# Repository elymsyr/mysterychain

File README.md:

# MysteryChain

A small hobby project: a virtual pet that lives on a keychain. A round 1.28" screen, a vibration motor and a tiny battery in a 3D-printed case about 4 cm across, paired with an Android app over Bluetooth.

- A pixel pet on the screen: a cat, or one of a few other characters picked in the app. It gets hungry, sleepy and happy through the day.
- Shake it and the pet plays; tap the case twice to pet it. It counts your steps too.
- Messages from your phone pop up in a speech bubble, along with the time, the weather and the song that's playing.
- One button: tap for the clock, hold to turn it on or off.

**Status:** works on the breadboard. The case is test-printed; nothing is assembled in it yet.

## Building one

Parts, wiring, flashing the firmware, the app and the case are in the [developer introduction](docs/developers.md).

## License

[GPL-3.0](LICENSE)

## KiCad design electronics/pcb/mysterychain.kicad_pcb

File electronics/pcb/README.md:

# MysteryChain PCB rev A

KiCad 9 project for the custom board that replaces the XIAO nRF52840 Sense build.
Design: [2026-10-20-pcb-design.md](../../docs/superpowers/specs/2026-10-20-pcb-design.md).

## Case v8 inputs

Case coordinates: origin = display centre, +X right, +Y toward the lug, looking at the display.
Front = display side, back = midframe side. The board is 1.0 mm thick.

| Item | Value |
| --- | --- |
| Outline | `gen_pcb.outline()`: circle r 18.0, cut at Y +7.0, J1 tongue X ±5.6 down to Y −18.2, Ø3.0 notches at r 17.6 / 205° and 335° |
| J1 (USB-C, back) | face on Y −18.2, X 0, opening −Y; GCT USB4105, 3.31 mm above the back face |
| H1, H2 | NPTH Ø2.0 at (−6.2, −14.8) and (6.2, −14.8): case v8 locating pins take the USB plug force |
| SW1 (button, back) | C&K KMS221GP side-actuated, body centre (−16.22, 0), plunger tip at X −18.37, axis Y 0, about 0.7 mm above the back face (half the 1.42 mm body) |
| SW2 (battery switch, back) | EG1390 body centre (−10.55, −7.0), slide along Y; v7 had (−11.25, −7.0): its pads would cut the 205° notch, so the slot moves 0.7 mm +X |
| SW3 (reset, back) | C&K PTS810 centre (8.6, −11.7), 2.5 mm tall; the midframe reset hole moves here (no room left of J1) |
| E73 (back) | body X −3.9…14.1, Y −8.2…4.8, 3.0 mm tall, antenna end at +X |
| J3 battery / J4 motor pads | back, top edge: J3 at (−13.5, 5.5) B+ / B−, J4 at (−9.5, 5.5) M+ / M− |
| J2 display pads | front, top edge, X −15.6…−3.6 at Y 5.5, pad 1 (VCC) at X −3.6 |
| U2 (IMU, front) | LSM6DS3TR-C at (−11.0, −1.4), rotation 0, on the front: its Z axis points at the display, opposite the XIAO's |

## ERC warnings kept

`check.py sch` fails on any ERC error and on any warning type not listed here.

| Warning | Where | Why it stays |
| --- | --- | --- |
| `pin_to_pin` | U1 pad 33 (P0.13, bidirectional) + PWR_FLAG on IMU_PWR | The IMU is powered from a GPIO (spec: 0 µA when off). The flag tells ERC the rail has a source. |
| `pin_to_pin` | U2 pins 1/2 (SA0, SDx, bidirectional) + PWR_FLAG on GND | SA0 and SDx are tied to GND on purpose (address 0x6A, aux bus unused). |

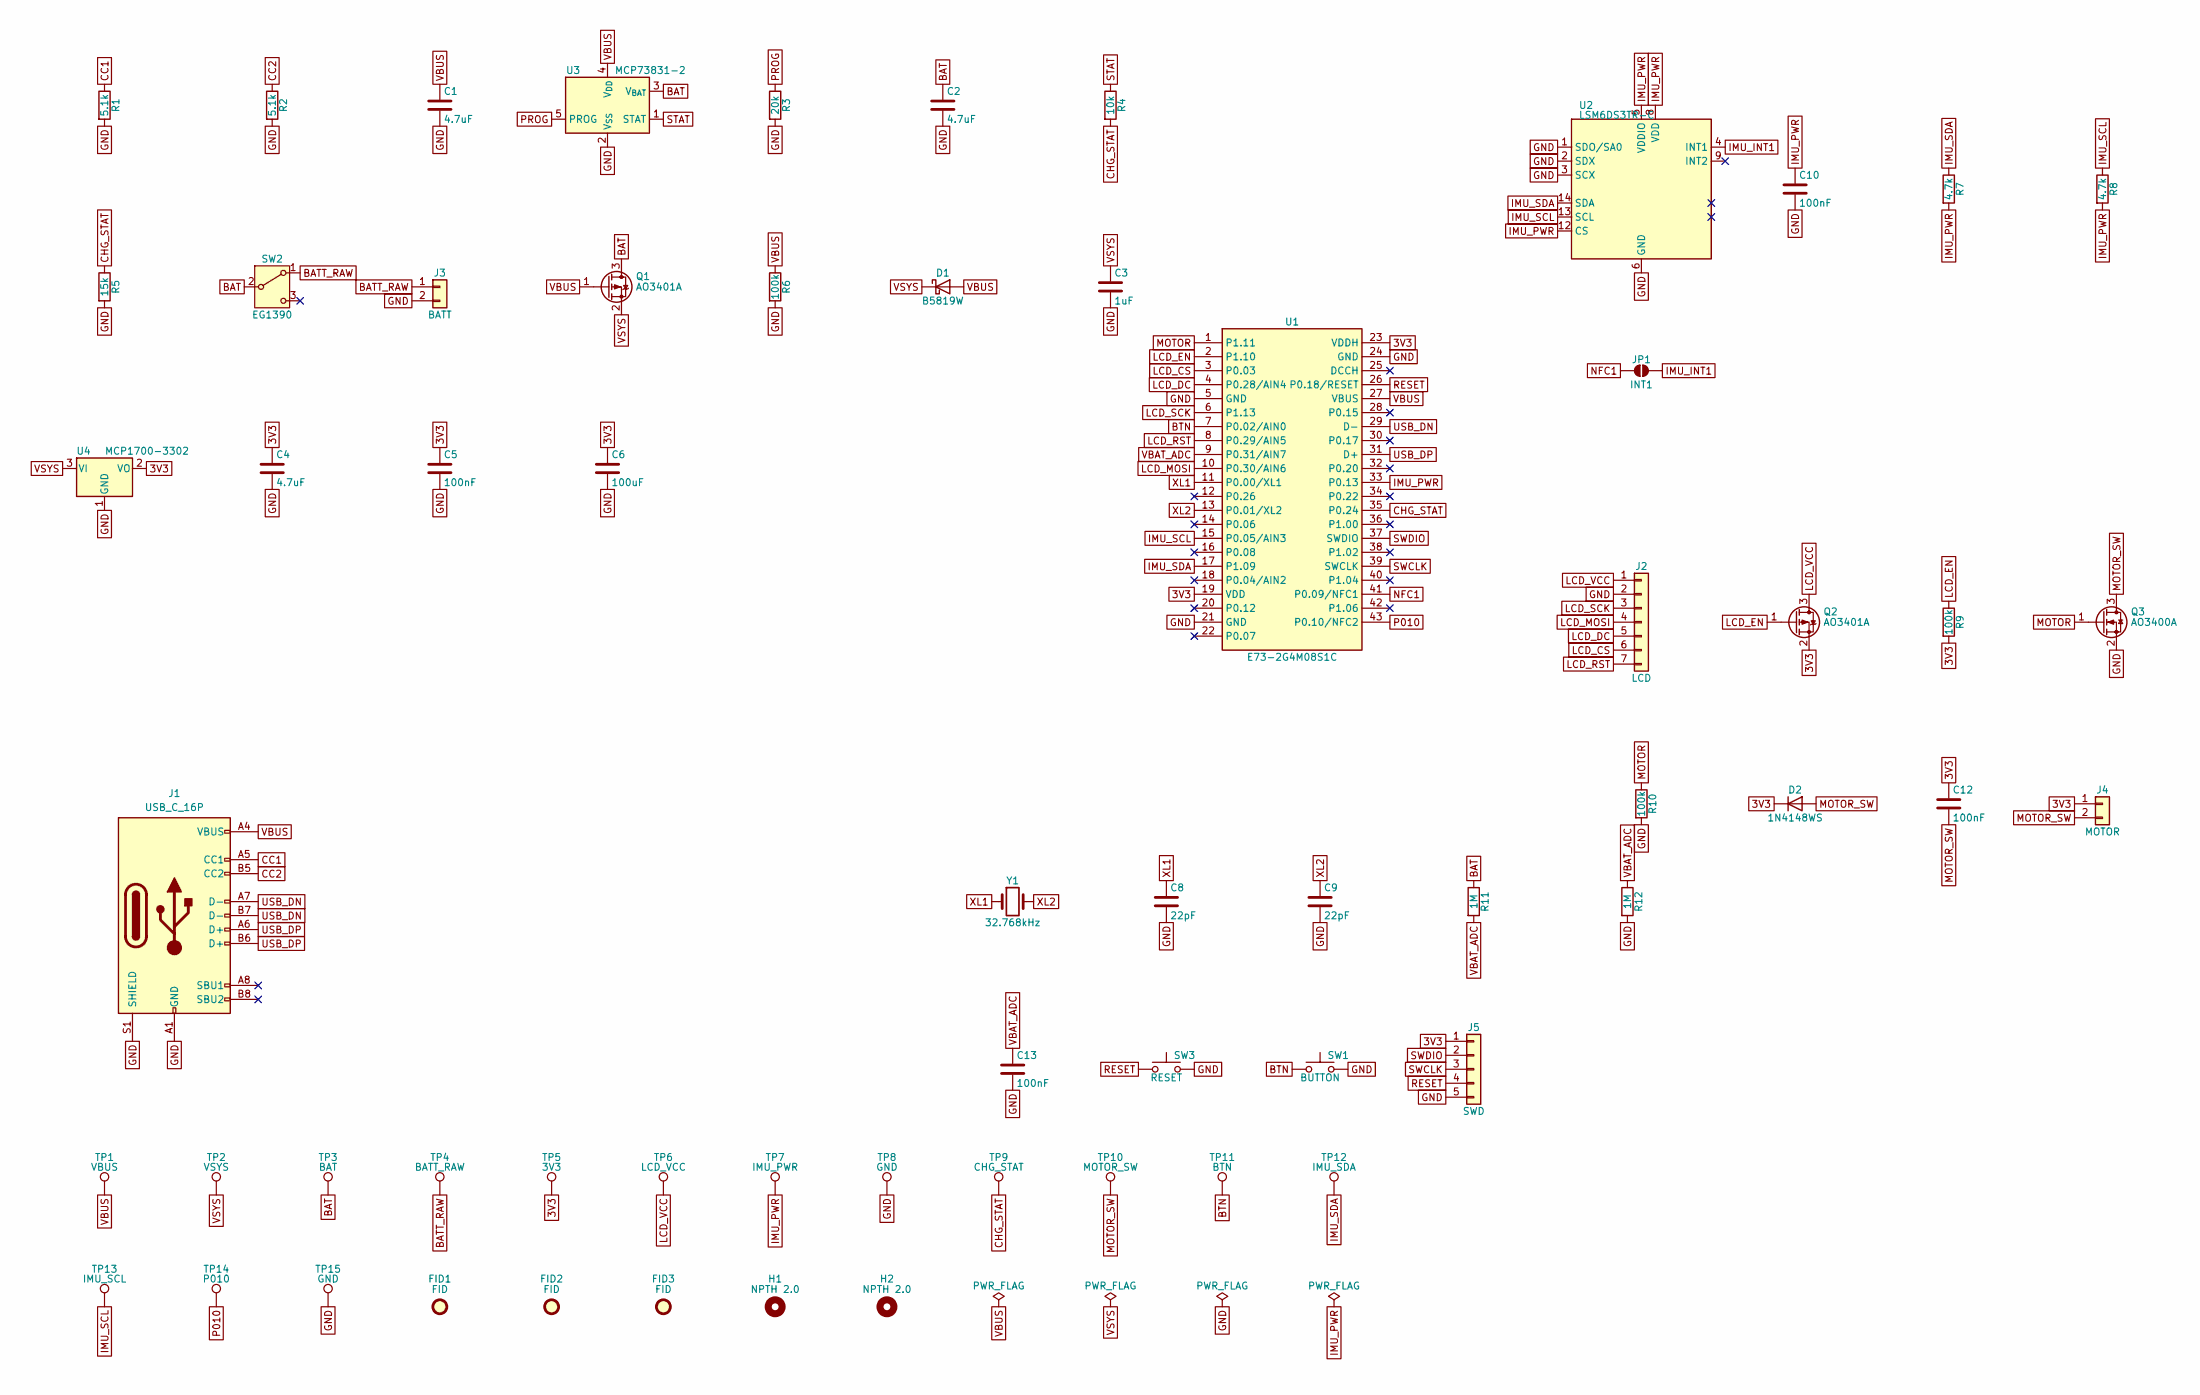
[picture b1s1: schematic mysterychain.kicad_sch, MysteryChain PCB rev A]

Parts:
C1, C2, C4: 4.7uF; C_0603_1608Metric; MPN 0603 X5R/X7R 10 V, 4.7uF
C3: 1uF; C_0603_1608Metric; MPN 0603 X5R/X7R 10 V, 1uF
C5, C10, C12, C13: 100nF; C_0603_1608Metric; MPN 0603 X5R/X7R 10 V, 100nF
C6: 100uF; C_1206_3216Metric; MPN Murata GRM31CR60J107KEA8L (1206 X5R 6.3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
C8, C9: 22pF; C_0603_1608Metric; MPN 0603 C0G 50 V, 22pF
D1: B5819W; D_SOD-123; MPN B5819W
D2: 1N4148WS; D_SOD-323; MPN 1N4148WS
FID1, FID2: FID; Fiducial_1mm_Mask2mm
FID3: FID; Fiducial_0.75mm_Mask1.5mm
H1, H2: NPTH 2.0; NPTH_D2.0mm
J1: USB_C_16P; USB_C_Receptacle_GCT_USB4105-xx-A_16P_TopMnt_Horizontal; MPN GCT USB4105-GF-A
J2: LCD; PadRow_1x07_P2.00mm; MPN wire pads: VCC GND SCL SDA DC CS RST (G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
J3: BATT; PadRow_1x02_P2.00mm; MPN wire pads (LiPo 402030 leads)
J4: MOTOR; PadRow_1x02_P2.00mm; MPN wire pads (vibration motor)
J5: SWD; PadRow_1x05_P2.54mm; MPN SWD pads 2.54 mm (pogo clip / held head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
JP1: INT1; SolderJumper-2_P1.3mm_Open_Pad1.0x1.5mm; MPN solder jumper, open
Q1, Q2: AO3401A; SOT-23; MPN AO3401A
Q3: AO3400A; SOT-23; MPN AO3400A
R1, R2: 5.1k; R_0603_1608Metric; MPN 0603 1% thick film, 5.1k (Yageo RC0603F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
R3: 20k; R_0603_1608Metric; MPN 0603 1% thick film, 20k (Yageo RC0603FR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
R4: 10k; R_0603_1608Metric; MPN 0603 1% thick film, 10k (Yageo RC0603FR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
R5: 15k; R_0603_1608Metric; MPN 0603 1% thick film, 15k (Yageo RC0603FR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
R6, R9, R10: 100k; R_0603_1608Metric; MPN 0603 1% thick film, 100k (Yageo RC0603F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
R7, R8: 4.7k; R_0603_1608Metric; MPN 0603 1% thick film, 4.7k (Yageo RC0603F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
R11, R12: 1M; R_0603_1608Metric; MPN 0603 1% thick film, 1M (Yageo RC0603FR-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
SW1: BUTTON; SW_SPST_CK_KMS2xxGP; MPN C&K KMS221GP LFS (side actuated)
SW2: EG1390; MPN E-Switch EG1390
SW3: RESET; SW_SPST_PTS810; MPN C&K PTS810SJK250SMTRLFS
TP1: VBUS; TestPad_D1.0mm; MPN bare pad
TP2: VSYS; TestPad_D1.0mm; MPN bare pad
TP3: BAT; TestPad_D1.0mm; MPN bare pad
TP4: BATT_RAW; TestPad_D1.0mm; MPN bare pad
TP5: 3V3; TestPad_D1.0mm; MPN bare pad
TP6: LCD_VCC; TestPad_D1.0mm; MPN bare pad
TP7: IMU_PWR; TestPad_D1.0mm; MPN bare pad
TP8, TP15: GND; TestPad_D1.0mm; MPN bare pad
TP9: CHG_STAT; TestPad_D1.0mm; MPN bare pad
TP10: MOTOR_SW; TestPad_D1.0mm; MPN bare pad
TP11: BTN; TestPad_D1.0mm; MPN bare pad
TP12: IMU_SDA; TestPad_D1.0mm; MPN bare pad
TP13: IMU_SCL; TestPad_D1.0mm; MPN bare pad
TP14: P010; TestPad_D1.0mm; MPN bare pad
U1: E73-2G4M08S1C; MPN Ebyte E73-2G4M08S1C
U2: LSM6DS3TR-C; LGA-14_3x2.5mm_P0.5mm_HandSolder; MPN ST LSM6DS3TR-C
U3: MCP73831-2; SOT-23-5; MPN MCP73831T-2ACI/OT
U4: MCP1700-3302; SOT-23; MPN MCP1700T-3302E/TT
Y1: 32.768kHz; Crystal_SMD_3215-2Pin_3.2x1.5mm; MPN RT3215-32.768-12.5-TR (CL 12.5 pF, 20 p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

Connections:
3V3: C4.1, C5.1, C6.1, C12.1, D2.1 (K), J4.1, J5.1, Q2.2 (S), R9.2, TP5.1, U1.19 (VDD), U1.23 (VDDH), U4.2 (VO)
BAT: C2.1, Q1.3 (D), R11.1, SW2.2 (B), TP3.1, U3.3 (V_{BAT})
BATT_RAW: J3.1, SW2.1 (A), TP4.1
BTN: SW1.1, TP11.1, U1.7 (P0.02/AIN0)
CC1: J1.A5 (CC1), R1.1
CC2: J1.B5 (CC2), R2.1
CHG_STAT: R4.2, R5.1, TP9.1, U1.35 (P0.24)
GND: C1.2, C2.2, C3.2, C4.2, C5.2, C6.2, C8.2, C9.2, C10.2, C13.2, J1.A1 (GND), J1.A12 (GND), J1.B1 (GND), J1.B12 (GND), J1.S1 (SHIELD), J2.2, J3.2, J5.5, Q3.2 (S), R1.2, R2.2, R3.2, R5.2, R6.2, R10.2, R12.2, SW1.2, SW3.2, TP8.1, TP15.1, U1.5 (GND), U1.21 (GND), U1.24 (GND), U2.1 (SDO/SA0), U2.2 (SDX), U2.3 (SCX), U2.6 (GND), U2.7 (GND), U3.2 (V_{SS}), U4.1 (GND)
IMU_INT1: JP1.2 (B), U2.4 (INT1)
IMU_PWR: C10.1, R7.2, R8.2, TP7.1, U1.33 (P0.13), U2.5 (VDDIO), U2.8 (VDD), U2.12 (CS)
IMU_SCL: R8.1, TP13.1, U1.15 (P0.05/AIN3), U2.13 (SCL)
IMU_SDA: R7.1, TP12.1, U1.17 (P1.09), U2.14 (SDA)
LCD_CS: J2.6, U1.3 (P0.03)
LCD_DC: J2.5, U1.4 (P0.28/AIN4)
LCD_EN: Q2.1 (G), R9.1, U1.2 (P1.10)
LCD_MOSI: J2.4, U1.10 (P0.30/AIN6)
LCD_RST: J2.7, U1.8 (P0.29/AIN5)
LCD_SCK: J2.3, U1.6 (P1.13)
LCD_VCC: J2.1, Q2.3 (D), TP6.1
MOTOR: Q3.1 (G), R10.1, U1.1 (P1.11)
MOTOR_SW: C12.2, D2.2 (A), J4.2, Q3.3 (D), TP10.1
NFC1: JP1.1 (A), U1.41 (P0.09/NFC1)
P010: TP14.1, U1.43 (P0.10/NFC2)
PROG: R3.1, U3.5 (PROG)
RESET: J5.4, SW3.1, U1.26 (P0.18/RESET)
STAT: R4.1, U3.1 (STAT)
SWCLK: J5.3, U1.39 (SWCLK)
SWDIO: J5.2, U1.37 (SWDIO)
USB_DN: J1.A7 (D-), J1.B7 (D-), U1.29 (D-)
USB_DP: J1.A6 (D+), J1.B6 (D+), U1.31 (D+)
VBAT_ADC: C13.1, R11.2, R12.1, U1.9 (P0.31/AIN7)
VBUS: C1.1, D1.2 (A), J1.A4 (VBUS), J1.A9 (VBUS), J1.B4 (VBUS), J1.B9 (VBUS), Q1.1 (G), R6.1, TP1.1, U1.27 (VBUS), U3.4 (V_{DD})
VSYS: C3.1, D1.1 (K), Q1.2 (S), TP2.1, U4.3 (VI)
XL1: C8.1, U1.11 (P0.00/XL1), Y1.1
XL2: C9.1, U1.13 (P0.01/XL2), Y1.2

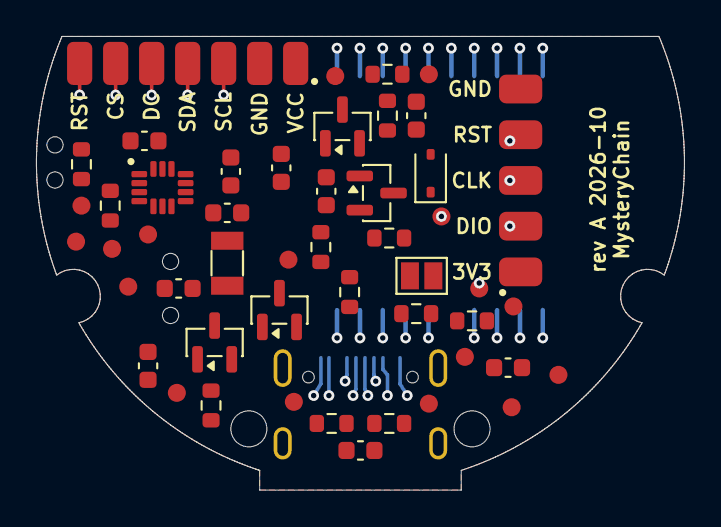
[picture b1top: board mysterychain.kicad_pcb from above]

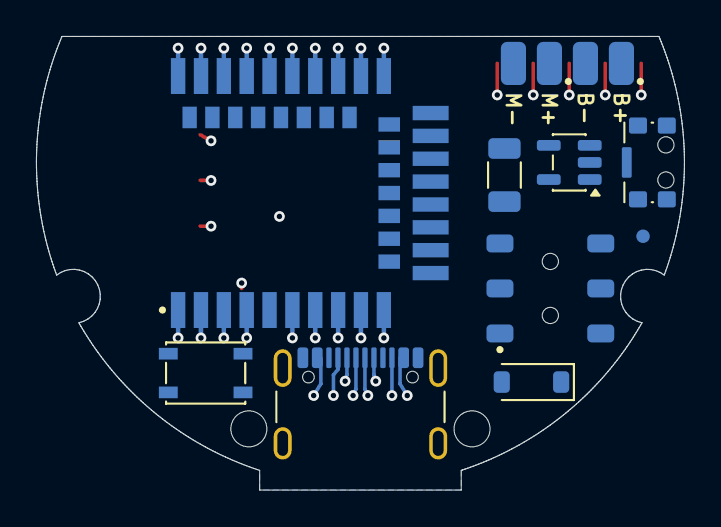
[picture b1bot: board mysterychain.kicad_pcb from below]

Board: 4 copper layers, 36.0 x 25.2 mm, 62 parts (11 on the bottom side), 35 nets.

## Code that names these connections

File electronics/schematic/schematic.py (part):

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    schematic_white.svg/.png          white background
    schematic_pnp_white.svg/.png      bench variant, USB power (no battery), Q2 = BC327 PNP (`schematic.py pnp`; writes only these)
    schematic_proto_white.svg/.png   first prototype with the parts in hand: Q2 = PJA3405, 5 mm tact button (`schematic.py proto0`)
Source of truth: ../README.md (pinout, motor driver, power)
"""
import sys
from pathlib import Path
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        left = ['D0', 'D1', 'D2', 'D3', 'D4', 'D5', 'D6']
        right = [('5V', '14', 'V5'), ('GND', '13', 'GND'), ('3V3', '12', 'V33'), ('D10', '11', 'D10'),
                 ('D9', '10', 'D9'), ('D8', '9', 'D8'), ('D7', '8', 'D7')]
        # 8 slots, bottom one empty (room for BAT labels); slot pitch = (H - 1) / 7 = S
        x = elm.Ic(size=(7, 1 + 7 * S), pins=[P(n, pin=str(i + 1), side='left', slot=f'{8 - i}/8') for i, n in enumerate(left)]
                   + [P(n, pin=p, side='right', slot=f'{8 - i}/8', anchorname=a) for i, (n, p, a) in enumerate(right)]
                   + [P('BAT+', side='bottom', slot='1/2', anchorname='BATP'), P('BAT−', side='bottom', slot='2/2', anchorname='BATN')])
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        elm.Line().at(x.D10).to((dx, x.D10.y)).label('SPI MOSI', fontsize=9)
        elm.Line().at(x.D8).to((dx, x.D8.y)).label('SPI SCK', fontsize=9)
        elm.Line().at(x.D7).right(1.5)
        elm.Tag().label('LCD_EN', fontsize=9)

        # ---- U2: GC9A01 display (pin no. = physical header order) ----
        # slot 2 empty: SDA lines up with U1 D10, SCL with D8
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            elm.Resistor().at(gdot.center).left(2.5).label('R4\n1 kΩ', loc='bottom')
        else:
            elm.Line().at(gdot.center).left(1.0)
        elm.Tag().left().label('LCD_EN', fontsize=9)

        # ---- U1 left: button and display control lines ----
        elm.Line().at(x.D0).left(0.8)
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        cnode = elm.Dot().at((q1.collector.x, q1.collector.y + 0.6))
        elm.Line().at(q1.collector).to(cnode.center)
        rail = cnode.center.y + 4.0
        elm.Motor().at(cnode.center).up(4.0).label('M1\n10×3\nvibration motor', loc='bottom', ofst=(0, -0.3))
        mtop = elm.Dot()
        elm.Vdd().label('3V3' if pnp else 'BAT+')  # off the LDO: its current sagged 3V3 and dimmed the display
        # D1: cathode (band) to the motor supply
        dxx = cnode.center.x - 2.2
        elm.Line().at(cnode.center).to((dxx, cnode.center.y))
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        else:
            elm.Dot().at(x.BATP)
            elm.Line().at(x.BATP).left(1.2)
            elm.Tag().left().label('BAT+', fontsize=9)  # motor supply
            elm.Switch().at(x.BATP).down(1.6).label('SW2\nbattery switch\nEG1390', loc='bottom', ofst=(0, 0.2))
            b1 = elm.BatteryCell().down(3.0).label('B1\nLiPo 402030\n3.7 V ~200 mAh\nprotected (PCM)', loc='bottom', ofst=(0, 0.3))
            text((b1.center.x - 0.45, b1.center.y + 0.35), '+', 12)  # long plate = positive
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        text((-13.5, title_y - 0.9), 'Pinout and notes: electronics/README.md · Build and tests: electronics/bring-up.md', 9,
             color='dimgray', halign='left')
        notes = [
            'Labels with the same name (LCD_CS, LCD_DC, LCD_RST, LCD_EN) are connected. All 3V3, BAT+ and GND symbols are one net each.',
            'Q1 BC337 legs: flat face toward you, legs down, left to right C–B–E (verify on your part with a diode test).',
            'M1 + and the D1 band (cathode) go to BAT+, not 3V3: on 3V3 the motor current sagged the LDO and dimmed the display. '
            'Firmware scales the PWM duty with VBAT so the 3 V motor sees ~3.1 V. Reversed, D1 shorts BAT+ to GND when Q1 turns on.',
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
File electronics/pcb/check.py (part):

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    pn = _pin_net()
    want = {
        "Q1": ["VBUS", "VSYS", "BAT"], "Q2": ["LCD_EN", "3V3", "LCD_VCC"], "Q3": ["MOTOR", "GND", "MOTOR_SW"],
        "D1": ["VSYS", "VBUS"], "D2": ["3V3", "MOTOR_SW"],  # pin 1 = K, 2 = A
        "U4": ["GND", "3V3", "VSYS"], "U3": ["STAT", "GND", "BAT", "VBUS", "PROG"],
    }
    for ref, ns in want.items():
        for i, n in enumerate(ns, 1):
            assert pn.get((ref, str(i))) == n, f"{ref} pin {i} is {pn.get((ref, str(i)))}, want {n}"
    for pin, n in {"1": "GND", "4": "IMU_INT1", "5": "IMU_PWR", "8": "IMU_PWR", "12": "IMU_PWR",
                   "13": "IMU_SCL", "14": "IMU_SDA"}.items():
        assert pn.get(("U2", pin)) == n, f"U2 pin {pin} is {pn.get(('U2', pin))}, want {n}"
    for pin in map(str, CASTELLATED):
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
